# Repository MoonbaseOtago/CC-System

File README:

(c) Copyright Paul Campbell paul@taniwha.com 2013

RF system software for CC2533 boards.

Documentation that used to live here is now at

	docs/index.html

or online at:

	http://www.moonbaseotago.com/cheaprf

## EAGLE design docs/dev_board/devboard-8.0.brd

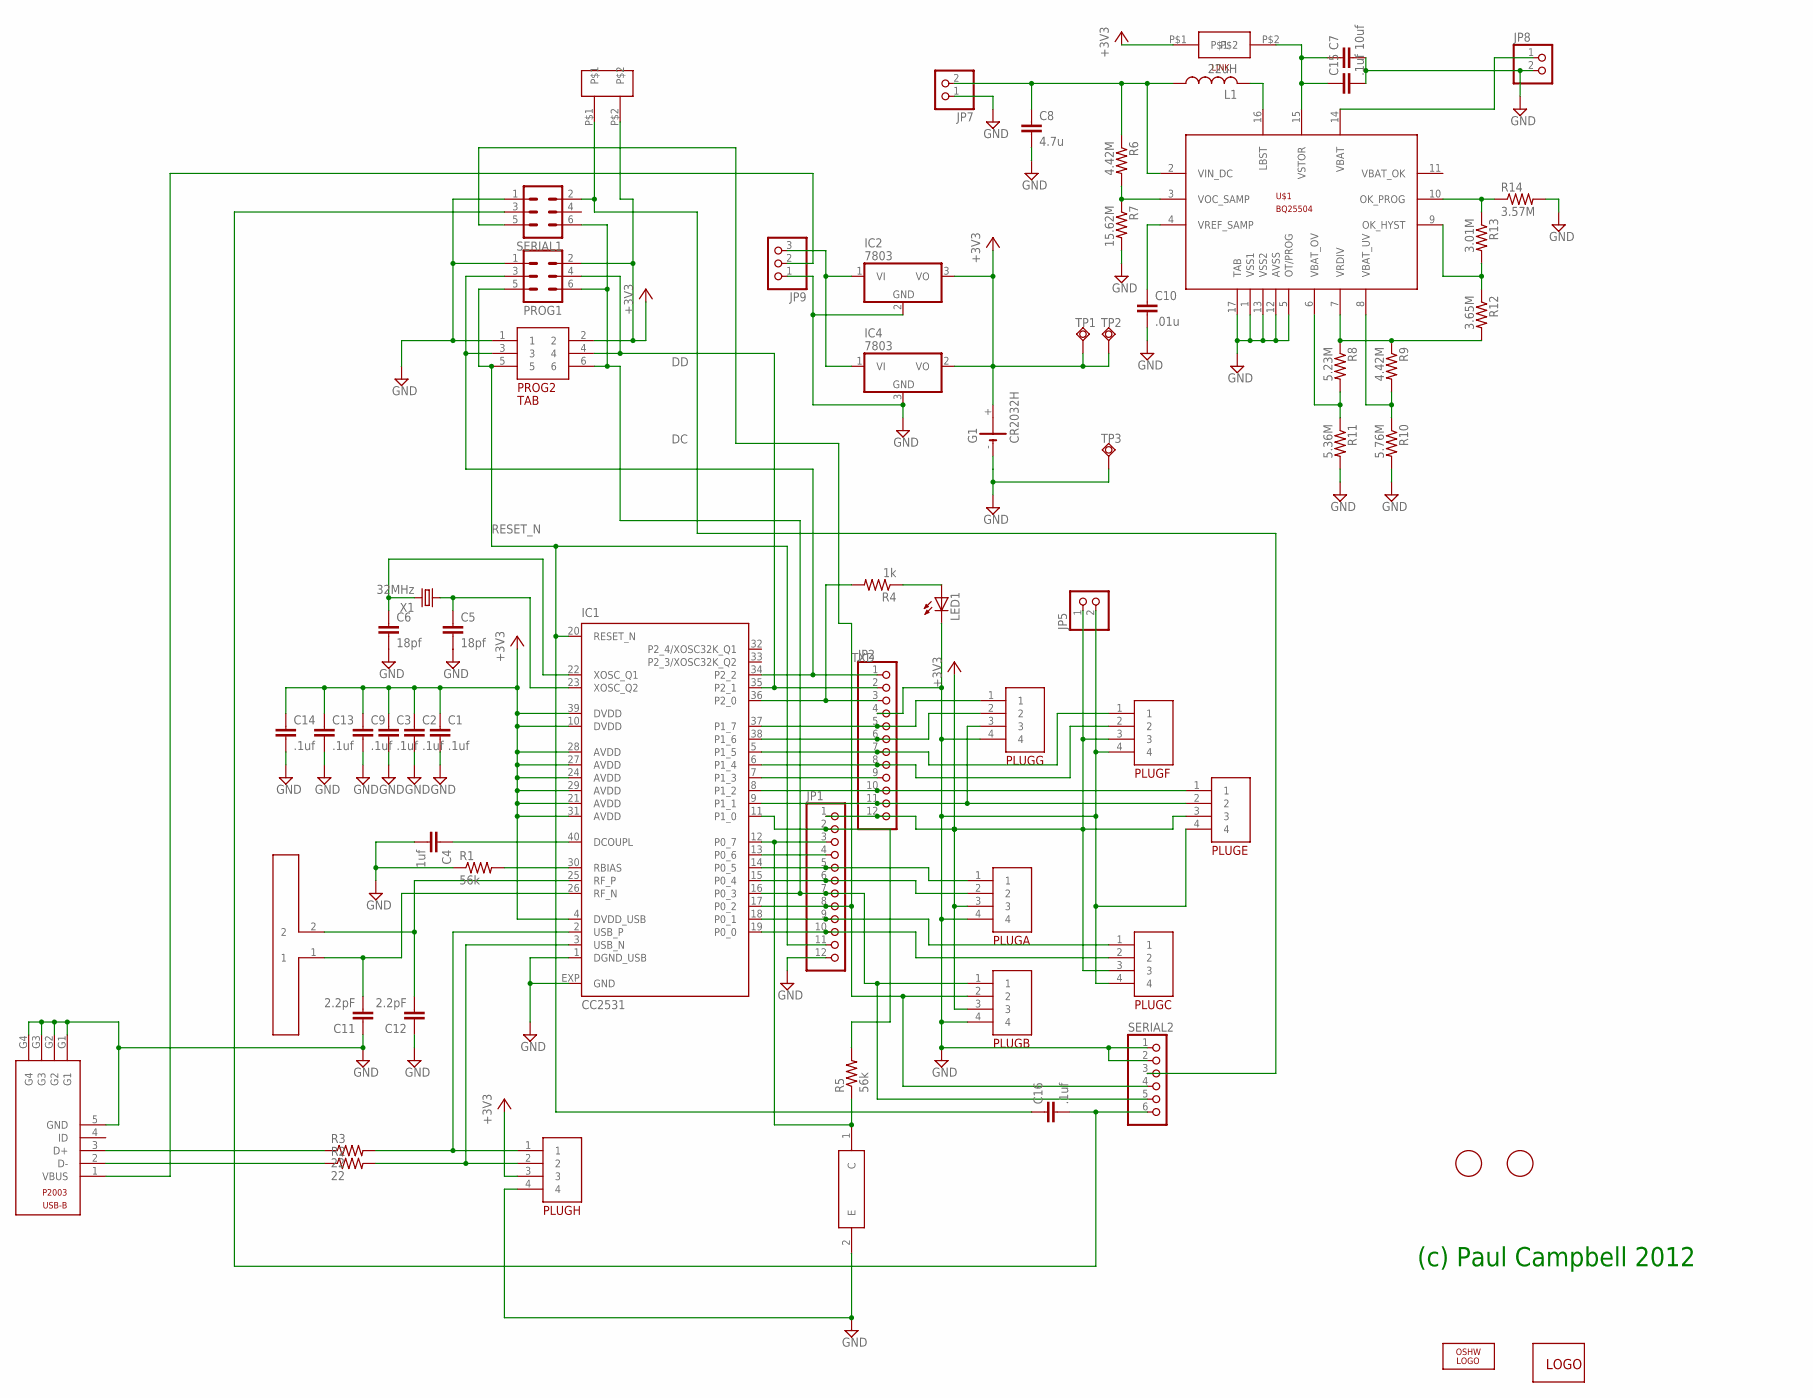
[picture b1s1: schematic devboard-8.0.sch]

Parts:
C1, C2, C3, C9, C13, C14, C15, C16: .1uf; C0603K
C4: 1uf; C0603K
C5, C6: 18pf; C0603
C7: 10uf; C1206
C8: 4.7u; C0603
C10: .01u; C0603
C11, C12: 2.2pF; C0402
G1: CR2032H
IC1: CC2531; RHA_S-PVQFN-N40
IC2: 7803; TO220V
IC4: 7803; TO252
JP1, JP2: PINHD-1X12-CB; 1X12-CB
JP5, JP7, JP8: PINHD-1X2; 1X02
JP9: PINHD-1X3; 1X03
L1: 22uH; L2012C
LED1: LEDCHIP-LED0603; CHIP-LED0603
LOGO1: OSHW_LOGO_FILLX0100-NT; OSHW_FILLX100_NOTEXT
P2003: FCI1018193-USBB
PLUGA: PIN4; PIN4-2MM
PLUGB: PIN4; PIN4-2MM
PLUGC: PIN4; PIN4-2MM
PLUGE: PIN4; PIN4-2MM
PLUGF: PIN4; PIN4-2MM
PLUGG: PIN4; PIN4-2MM
PLUGH: PIN4; PIN4-2MM
PROG1: MA03-2
PROG2: TAB; TAG
Q1: KDT
R1, R5: 56k; R0603
R2, R3: 22; R0603
R4: 1k; R0603
R6, R9: 4.42M; R0603
R7: 15.62M; R0603
R8: 5.23M; R0603
R10: 5.76M; R0603
R11: 5.36M; R0603
R12: 3.65M; R0603
R13: 3.01M; R0603
R14: 3.57M; R0603
SERIAL1: MA03-2
SERIAL2: PINHD-1X6; 1X06
SERIAL-POWER: 2-PAD
TP1, TP2, TP3: TPSQPAD1-13; P1-13
U$1: BQ25504; QF16
U$2, U$18: FIDUCIAL; FIDUCIAL_1MM
U$3: DIPOLEDIPOLE1; DIPOLE
U$4: 2-PAD-LINK
U$5: MOONBASE-LOGO
X1: 32MHz; SM49

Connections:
+3V3: C1.1, C2.1, C3.1, C9.1, C13.1, C14.1, G1.+, IC1.4 (DVDD_USB), IC1.10 (DVDD), IC1.21 (AVDD), IC1.24 (AVDD), IC1.27 (AVDD), IC1.28 (AVDD), IC1.29 (AVDD), IC1.31 (AVDD), IC1.39 (DVDD), IC2.3 (VO), IC4.2 (VO), JP1.1, JP2.12, JP5.1, PLUGA.3, PLUGB.3, PLUGC.3, PLUGE.3, PLUGF.3, PLUGH.3, PROG1.2, PROG2.2, SERIAL-POWER.P$2, TP1.TP, TP2.TP, U$4.P$1
DC: IC1.34 (P2_2), JP2.1, PROG1.3, PROG2.3
DD: IC1.35 (P2_1), JP2.2, PROG1.4, PROG2.4
GND: C1.2, C2.2, C3.2, C4.2, C5.2, C6.2, C7.2, C8.2, C9.2, C10.2, C11.1, C12.1, C13.2, C14.2, C15.2, G1.-, IC1.1 (DGND_USB), IC1.EXP (GND), IC2.2 (GND), IC4.3 (GND), JP1.12, JP2.4, JP5.2, JP7.1, JP8.2, JP9.1, LED1.C, P2003.5 (GND), P2003.G1, P2003.G2, P2003.G3, P2003.G4, PLUGA.4, PLUGB.4, PLUGC.4, PLUGE.4, PLUGF.4, PLUGG.4, PLUGH.4, PROG1.1, PROG2.1, Q1.2 (E), R1.1, R7.2, R10.2, R11.2, R14.2, SERIAL1.1, SERIAL2.1, SERIAL2.2, TP3.TP, U$1.1 (VSS1), U$1.5 (OT/PROG), U$1.12 (AVSS), U$1.13 (VSS2), U$1.17 (TAB)
unnamed: LED1.A, R4.1
unnamed: JP9.2, P2003.1 (VBUS)
unnamed: IC1.2 (USB_P), PLUGH.1, R3.2
unnamed: P2003.2 (D-), R2.1
unnamed: IC1.3 (USB_N), PLUGH.2, R2.2
unnamed: SERIAL1.2, SERIAL2.3, SERIAL-POWER.P$1
unnamed: P2003.3 (D+), R3.1
unnamed: IC1.11 (P1_0), JP1.2, R5.2
unnamed: IC2.1 (VI), IC4.1 (VI), JP9.3
unnamed: C4.1, IC1.40 (DCOUPL)
unnamed: IC1.13 (P0_6), JP1.4
unnamed: IC1.14 (P0_5), JP1.5, PLUGA.1
unnamed: C7.1, C15.1, U$1.15 (VSTOR), U$4.P$2
unnamed: IC1.18 (P0_1), JP1.9, PLUGC.1
unnamed: IC1.19 (P0_0), JP1.10, PLUGC.2
unnamed: IC1.9 (P1_1), JP2.11, PLUGE.2, PLUGG.3
unnamed: IC1.8 (P1_2), JP2.10, PLUGE.1
unnamed: C6.1, IC1.22 (XOSC_Q1), X1.2
unnamed: C5.1, IC1.23 (XOSC_Q2), X1.1
unnamed: IC1.12 (P0_7), JP1.3, Q1.1 (C), R5.1
unnamed: IC1.7 (P1_3), JP2.9
unnamed: IC1.30 (RBIAS), R1.2
unnamed: IC1.6 (P1_4), JP2.8, PLUGF.2
unnamed: C12.2, IC1.25 (RF_P), U$3.2
unnamed: C11.2, IC1.26 (RF_N), U$3.1
unnamed: IC1.5 (P1_5), JP2.7, PLUGF.1
unnamed: IC1.38 (P1_6), JP2.6, PLUGG.2
unnamed: IC1.37 (P1_7), JP2.5, PLUGG.1
unnamed: IC1.36 (P2_0), JP2.3, R4.2
unnamed: IC1.15 (P0_4), JP1.6, PLUGA.2
unnamed: C16.2, SERIAL1.3, SERIAL2.6
unnamed: L1.2, U$1.16 (LBST)
unnamed: C8.1, JP7.2, L1.1, R6.1, U$1.2 (VIN_DC)
unnamed: JP8.1, U$1.14 (VBAT)
unnamed: R6.2, R7.1, U$1.3 (VOC_SAMP)
unnamed: C10.1, U$1.4 (VREF_SAMP)
unnamed: R8.2, R11.1, U$1.6 (VBAT_OV)
unnamed: R9.2, R10.1, U$1.8 (VBAT_UV)
unnamed: R13.1, R14.1, U$1.10 (OK_PROG)
unnamed: R8.1, R9.1, R12.2, U$1.7 (VRDIV)
unnamed: R12.1, R13.2, U$1.9 (OK_HYST)
RESET_N: C16.1, IC1.20 (RESET_N), JP1.11, PROG1.5, PROG2.5
RXD: IC1.17 (P0_2), JP1.8, PLUGB.2, SERIAL1.5, SERIAL2.4
TXD: IC1.16 (P0_3), JP1.7, PLUGB.1, PROG1.6, PROG2.6, SERIAL1.6, SERIAL2.5

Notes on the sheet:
(c) Paul Campbell 2012

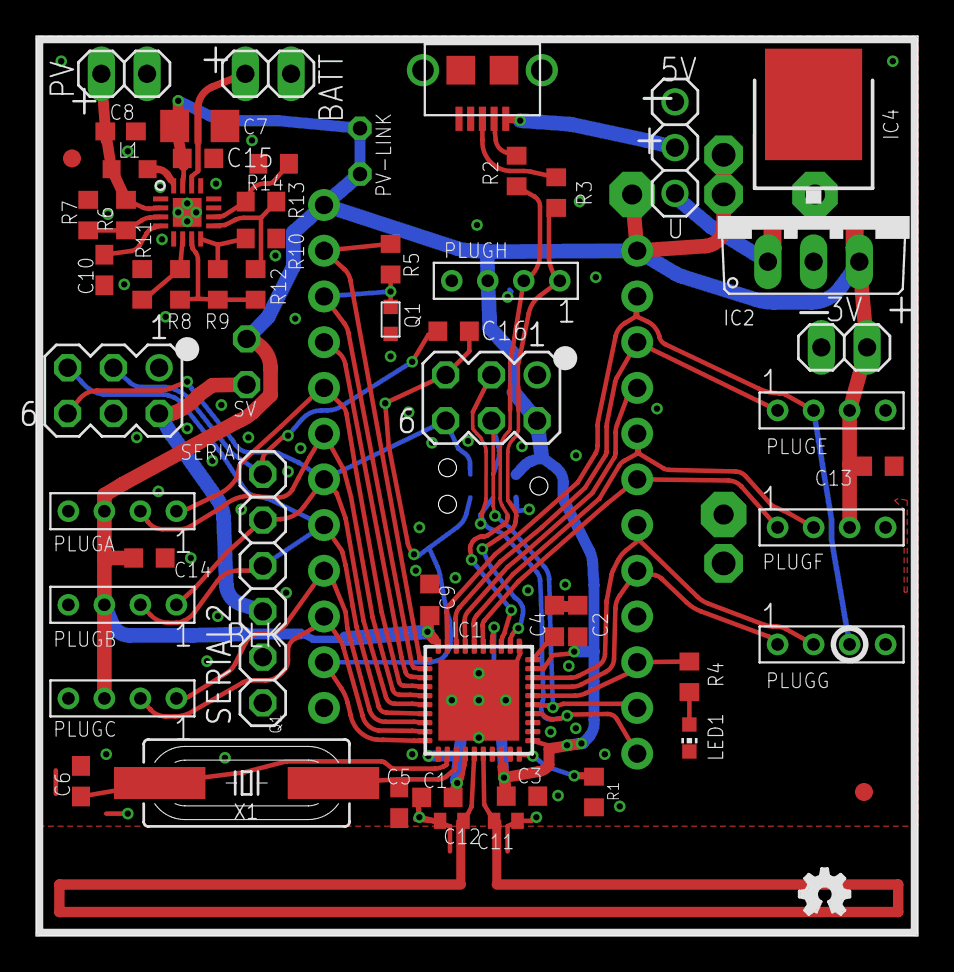
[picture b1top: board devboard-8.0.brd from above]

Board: 2 copper layers, 49.0 x 50.0 mm, 67 parts (1 on the bottom side), 48 nets.

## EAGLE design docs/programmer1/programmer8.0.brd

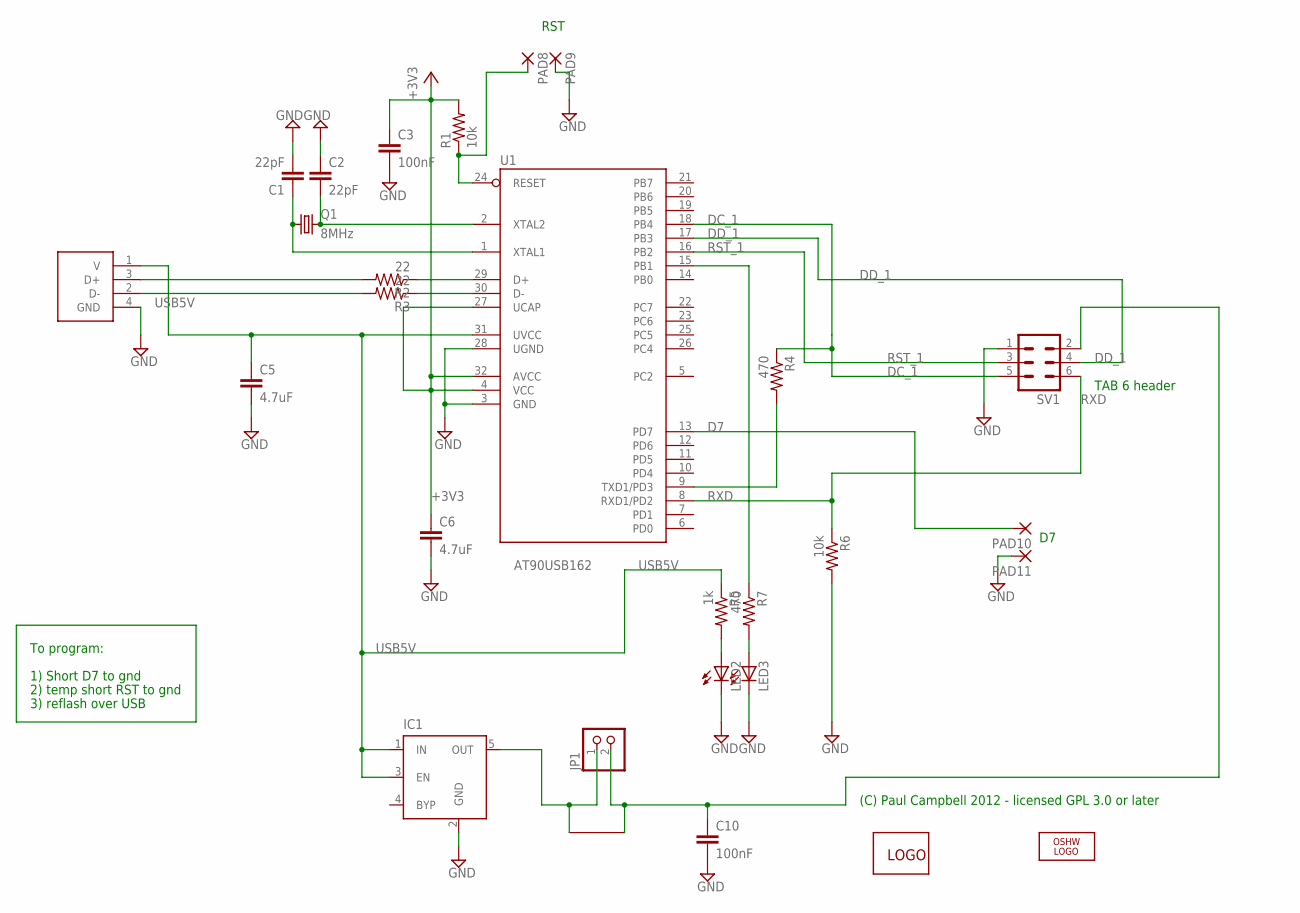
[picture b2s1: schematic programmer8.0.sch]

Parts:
C1, C2: 22pF; C0603
C3, C10: 100nF; C0603
C5, C6: 4.7uF; C0805
IC1: MIC5219XX; SOT23-5
JP1: PINHD-1X2; 1X02
LED2, LED3: LEDCHIP-LED0805; CHIP-LED0805
LOGO2: OSHW_LOGO_FILLX0100-NT; OSHW_FILLX100_NOTEXT
PAD8, PAD9, PAD10, PAD11: 1,6/0,8
Q1: 8MHz; HC49UP
R1, R6: 10k; R0603
R2, R3: 22; R0603
R4, R7: 470; R0603
R5: 1k; R0603
SV1: MA03-2
U1: AT90USB162; TQFP32-08
U$1: LINK
U$2: MOONBASE-LOGO
U$3: USB-RAW; RAW-USB

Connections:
+3V3: C3.1, C6.1, R1.2, U1.4 (VCC), U1.27 (UCAP), U1.32 (AVCC)
D7: PAD10.1, U1.13 (PD7)
DC_1: R4.1, SV1.5, U1.18 (PB4)
DD_1: SV1.4, U1.17 (PB3)
GND: C1.2, C2.1, C3.2, C5.2, C6.2, C10.2, IC1.2 (GND), LED2.C, LED3.C, PAD9.1, PAD11.1, R6.2, SV1.1, U1.3 (GND), U1.28 (UGND), U$3.4 (GND)
unnamed: C1.1, Q1.1, U1.1 (XTAL1)
unnamed: C2.2, Q1.2, U1.2 (XTAL2)
unnamed: R2.1, U1.29 (D+)
unnamed: R3.1, U1.30 (D-)
unnamed: R4.2, U1.9 (TXD1/PD3)
unnamed: IC1.5 (OUT), JP1.1, U$1.1
unnamed: C10.1, JP1.2, SV1.2, U$1.2
unnamed: R3.2, U$3.2 (D-)
unnamed: R2.2, U$3.3 (D+)
unnamed: LED2.A, R5.2
unnamed: LED3.A, R7.2
unnamed: R7.1, U1.15 (PB1)
RST: PAD8.1, R1.1, U1.24 (RESET)
RST_1: SV1.3, U1.16 (PB2)
RXD: R6.1, SV1.6, U1.8 (RXD1/PD2)
USB5V: C5.1, IC1.1 (IN), IC1.3 (EN), R5.1, U1.31 (UVCC), U$3.1 (V)

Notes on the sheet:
(C) Paul Campbell 2012 - licensed GPL 3.0 or later
RST
To program:
1) Short D7 to gnd
2) temp short RST to gnd
3) reflash over USB
TAB 6 header

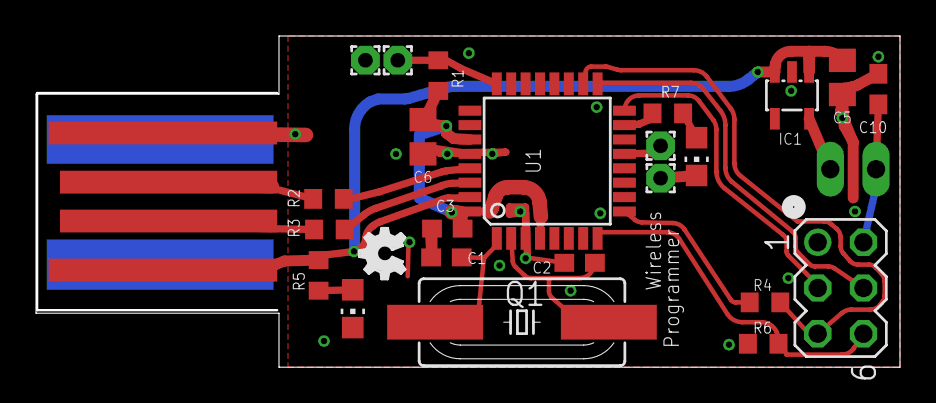
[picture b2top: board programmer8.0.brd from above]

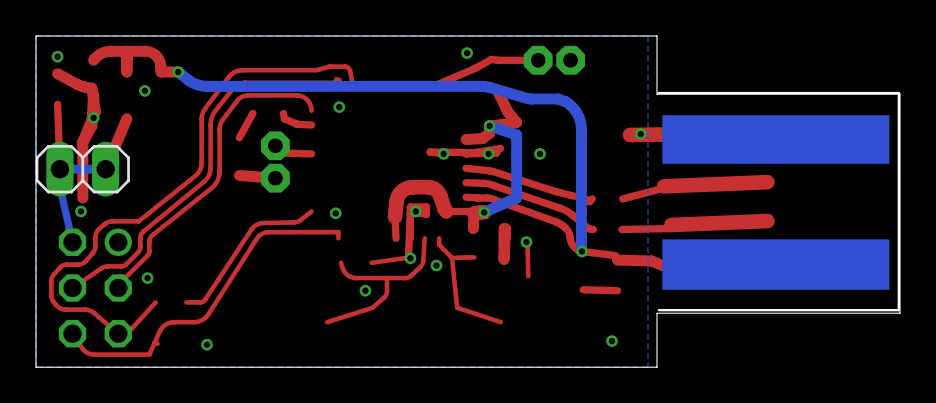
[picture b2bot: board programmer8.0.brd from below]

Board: 2 copper layers, 48.0 x 18.4 mm, 28 parts (2 on the bottom side), 21 nets.

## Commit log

2013-06-16 commit first files for backup
2013-06-16 add copyrights
2013-06-18 add more copyright stuff, first hack at API documentation
2013-06-19 clean up file hierarchy
2013-06-30 changes to add mac addresses to the API, more serial interface API
2013-07-09 push latest changes
2013-07-10 changes to clean up register usage during interrupts, don't step on SDCC
2013-07-12 got serial pcket protocol working
2013-07-16 save current system state - added scriptable serial interface
2013-07-17 fix receive bug introduced during memory optimisation
2013-07-18 changes to disable SUOTA auto-packet fill
2013-07-19 fix stupid bug in receive path
2013-07-19 fix issues with mac addresses and mac reporting
2013-08-05 got first set of crypto working - note that the app API for crypto call back has changed - no one's using it yet but if you've copied the sample_app you should update APP_GET_KEY
2013-08-05 reenable final crypto sum check
2013-08-06 changed the RF API to support multiple crypto keys - WARNING the API has changed for rf_send
2013-08-12 fix problem that caused low memory to be trashed (and saved parameter data to be lost)
2013-08-13 Convert RF receive path and crypto path to assembler - kernel now fits in ROM with 1K to spare
2013-08-18 reworked Makefiles to build kernel and apps - for the moment you should continue to build unified builds
2013-09-03 partial changes for SUOTA - protocol is working, but no flash writes yet bug fixes to kernel scheduler and rf send/receive code
2013-09-23 SUOTA changes - first working release
2013-09-23 add Makefile and source changes to remove leds/key/daylight drivers from the base kernel
2013-09-24 add macros to implement a simple Arduino-like GPIO interface
2013-09-25 clear interrupt vectors during suota non-reset restart
2013-09-26 minor API tweaks for docs, make SUOTA more picky about loaded images
2013-09-27 add suota test scripts
2013-09-27 paramaterise the location of the installed SDCC
2013-09-28 fix a task schedulding bug, add more sample code
2013-09-28 new documenation
2013-09-28 fix minor documentation bugs
2013-09-28 fix more web page typos
2013-10-04 update documentation
2013-10-04 save IP gateway code (not working yet)
2013-10-06 fix bug in memory allocation for LEDs driver
2013-10-06 More changes to make Makefile easier to use
2013-10-06 changes to makefile to allow automatic build/push from the makefile
2013-10-06 minor documentation fix
2013-10-06 fix key handling bug in serial RPC library
2013-10-06 add -I flag to serial gateway to send quick commands
2013-10-08 Add API for power management
2013-10-09 documentation for the latest release of the programmer GUI
2013-10-10 minor doumentation changes
2013-10-10 Lock command is working update the docs
2013-10-10 more minor cosmetic documentation changes
2013-10-12 fix buffer issue when using suota key, add minor documentation change
2013-10-19 minor docs changes, test code for manufacture
2013-10-26 push minor docs fix
2013-11-03 fix problem with keyboard driver
2013-12-08 fix bug with sleeping and losing keys, add a way to tell suota is happening
2013-12-08 fix bug in __bit allocation
2013-12-08 add more serial interface debug, all allow K 254 ...
2013-12-24 add change to keep CPU awake when sending SUOTA to someone else
2014-03-18 Fix problem with timer queue in very low power states
2014-05-20 Fix problem with key caching in the serial gateway firmware
